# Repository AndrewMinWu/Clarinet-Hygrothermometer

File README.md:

# Clarinet Hygrothermometer

<table> <tr> <td></td> <td></td> </tr> </table>

## Repository Structure

```text
├── hardware/          # Schematic, PCB, and gerber files
├── firmware/          # ESP-IDF C, using VSCode
└── docs/              # Datasheets
```

## Purpose & Motivation:
Having played the clarinet for over 8 years, I've grown to love my wooden instrument. However, in February of 2026, my instrument cracked due to a sudden drop in humidity (as my technician pointed out that wintertime brings dryer air). Thus, to prevent future issues and to save money from expensive repairs, I designed a PCB to accurately monitor the humidity and temperature within my clarinet case.

## Design

### Component List (BOM)
1. ESP32-C3-WROOM-02 ([Datasheet](https://www.espressif.com/sites/default/files/documentation/esp32-c3-wroom-02_datasheet_en.pdf))
2. MCP73831-2-OT Charge Controller ([Datasheet](https://ww1.microchip.com/downloads/en/DeviceDoc/20001984g.pdf))
3. AP2112K-3.3 LDO Voltage Regulator ([Datasheet](https://www.diodes.com/assets/Datasheets/AP2112.pdf))
4. GCT USB4105-GF-A USB-C Receptacle 16P SMD RA ([Datasheet](https://gct.co/files/drawings/usb4105.pdf))
5. SHT31 Humidity & Temperature Sensor ([Datasheet](https://sensirion.com/media/documents/213E6A3B/63A5A569/Datasheet_SHT3x_DIS.pdf))
6. OLED Display Breakout Board (4-pin I2C) ([Datasheet](https://cdn-shop.adafruit.com/datasheets/SSD1306.pdf))
7. 3.7V 1100mAh (4.1Wh) Lithium-Polymer Battery
8. SHT31 Breakout Board (4-pin I2C)
9. Passives & Miscellaneous Hardware:
   - Capacitors (0805, Ceramic)
   - Resistors (0805)
   - Charing Indicator LED
   - Push Buttons

### PCB, Schematic, Finished Board
The Schematic and PCB were designed in Altium. 

<table width="100%">
  <tr>
    <td width="50%"></td>
    <td width="50%"></td>
</table>

### Measurements

 I tested the accuracy of the SHT31 by putting the board in an enclosed tupperware container with a 49% Boveda humidity pack, and with a small vertical glass thermometer. I found the following:
* **Relative Humidity:** Accurate to ±2%.
* **Temperature:** Consistently reads ~0.8°C high. I believe this exceeds datasheet tolerances due to the sensor picking up some heat dissipated by the ESP32 (due to their proximity).

### Firmware
* **Language & Framework:** C / ESP-IDF, built in VSCode with PlatformIO (no external libraries)
* **I2C Configuration:** Bus at 100 kHz
* **Peripherals:** SHT31 temperature/humidity sensor and SSD1306 OLED
* **Display Driver:** Direct SSD1306 register setup with a 1024-byte static buffer
* **Font & Graphics:** Rendering using a custom 5x7 ASCII lookup table scaled 2x
* **Sampling & Control:** 2 Hz polling loop
## Assembly & Demonstration

**Short Demo**  
<video src="https://github.com/user-attachments/assets/3b9bc241-1b57-4820-86a4-abee198bdf83" width="100%" controls></video>

* **Assembly:** Hand-soldered all parts and tested the board with a multimeter (checking all voltage readings: VBAT, 3v3, 5V and ensuring no shorts) before flashing firmware.

## Active Development

* **Power Optimization:** Moving to deep-sleep mode to extend battery life beyond the current ~30-hour calculated runtime.
* **Data Logging:** Adding BLE (Bluetooth Low Energy) services to stream the SHT31 readings to my phone to monitor changes over time (i.e. how does the humidity change depending on the season?).

<div align="center">
  <p><strong>My messy home workbench</strong></p>
  
</div>

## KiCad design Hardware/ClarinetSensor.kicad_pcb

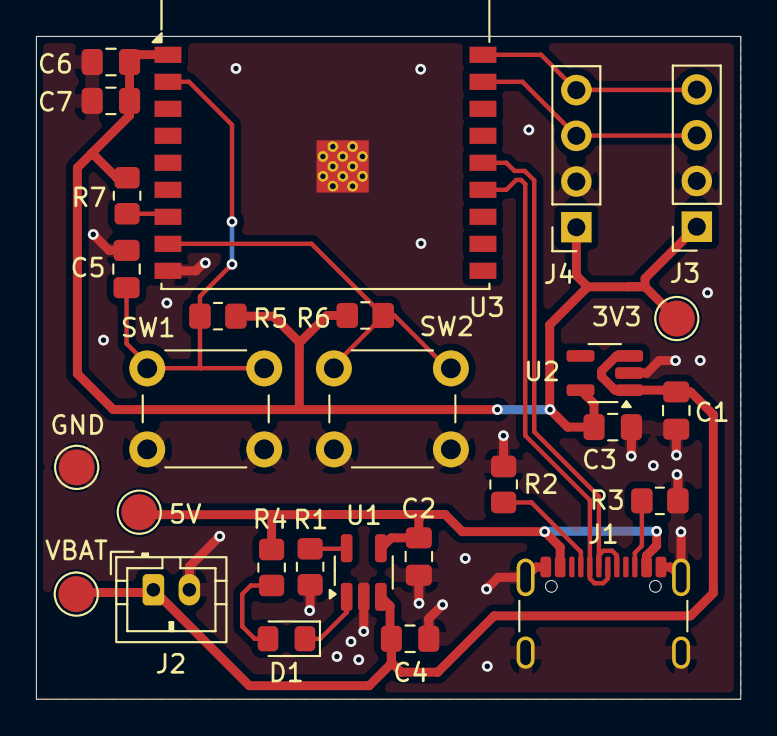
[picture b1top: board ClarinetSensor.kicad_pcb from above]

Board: 2 copper layers, 39.1 x 36.8 mm, 28 parts (0 on the bottom side), 16 nets.

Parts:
3V3: 3.3V; TestPoint_Pad_D2.0mm
5V: 5V; TestPoint_Pad_D2.0mm
C1, C3, C5: 1u; C_0805_2012Metric_Pad1.18x1.45mm_HandSolder
C2, C4: 4.7u; C_0805_2012Metric_Pad1.18x1.45mm_HandSolder
C6: 0.1u; C_0805_2012Metric_Pad1.18x1.45mm_HandSolder
C7: 10u; C_0805_2012Metric_Pad1.18x1.45mm_HandSolder
D1: LED; LED_0805_2012Metric_Pad1.15x1.40mm_HandSolder
GND: GND; TestPoint_Pad_D2.0mm
J1: USB_C_Receptacle_USB2.0_16P; USB_C_Receptacle_GCT_USB4105-xx-A_16P_TopMnt_Horizontal
J2: Conn_01x02; JST_PH_B2B-PH-K_1x02_P2.00mm_Vertical
J3, J4: Conn_01x04; PinSocket_1x04_P2.54mm_Vertical
R1: 4.7k; R_0805_2012Metric_Pad1.20x1.40mm_HandSolder
R2, R3: 5.1k; R_0805_2012Metric_Pad1.20x1.40mm_HandSolder
R4: 1k; R_0805_2012Metric_Pad1.20x1.40mm_HandSolder
R5, R6, R7: 10k; R_0805_2012Metric_Pad1.20x1.40mm_HandSolder
SW1, SW2: SW_Push; SW_PUSH_6mm_H5mm
U1: MCP73831-2-OT; SOT-23-5_HandSoldering
U2: AP2112K-3.3; SOT-23-5_HandSoldering
U3: ESP32-C3-WROOM-02
VBAT: VBAT; TestPoint_Pad_D2.0mm

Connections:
+3.3V: 3V3.1 (1_1), C3.1, C6.1, C7.1, J3.1, J4.1, R5.1, R6.1, R7.1, U2.5 (VOUT), U3.1 (3V3)
+5V: 5V.1 (1_1), C2.2, J1.A4 (VBUS), J1.A9 (VBUS), J1.B4 (VBUS), J1.B9 (VBUS), R4.2, U1.4 (V_{DD})
D+: J1.A6 (D+), J1.B6 (D+), U3.14 (IO19)
D-: J1.A7 (D-), J1.B7 (D-), U3.13 (IO18)
EN: C5.1, R5.2, SW1.1, U3.2 (EN)
GND: C1.2, C2.1, C3.2, C4.2, C5.2, C6.2, C7.2, GND.1 (1_1), J1.A1 (GND), J1.A12 (GND), J1.B1 (GND), J1.B12 (GND), J1.SH (SHIELD), J2.2, J3.2, J4.2, R1.1, R2.1, R3.1, SW1.2, SW2.2, U1.2 (V_{SS}), U2.2 (GND), U3.9 (GND), U3.19 (GND)
IO9: R6.2, SW2.1, U3.8 (IO9)
unnamed: D1.2 (A), R4.1
unnamed: D1.1 (K), U1.1 (STAT)
unnamed: J1.A5 (CC1), R2.2
unnamed: J1.B5 (CC2), R3.2
unnamed: R1.2, U1.5 (PROG)
unnamed: R7.2, U3.7 (IO8)
SCL: J3.3, J4.3, U3.17 (IO1)
SDA: J3.4, J4.4, U3.18 (IO0)
VBAT: C1.1, C4.1, J2.1, U1.3 (V_{BAT}), U2.1 (VIN), U2.3 (EN), VBAT.1 (1_1)
